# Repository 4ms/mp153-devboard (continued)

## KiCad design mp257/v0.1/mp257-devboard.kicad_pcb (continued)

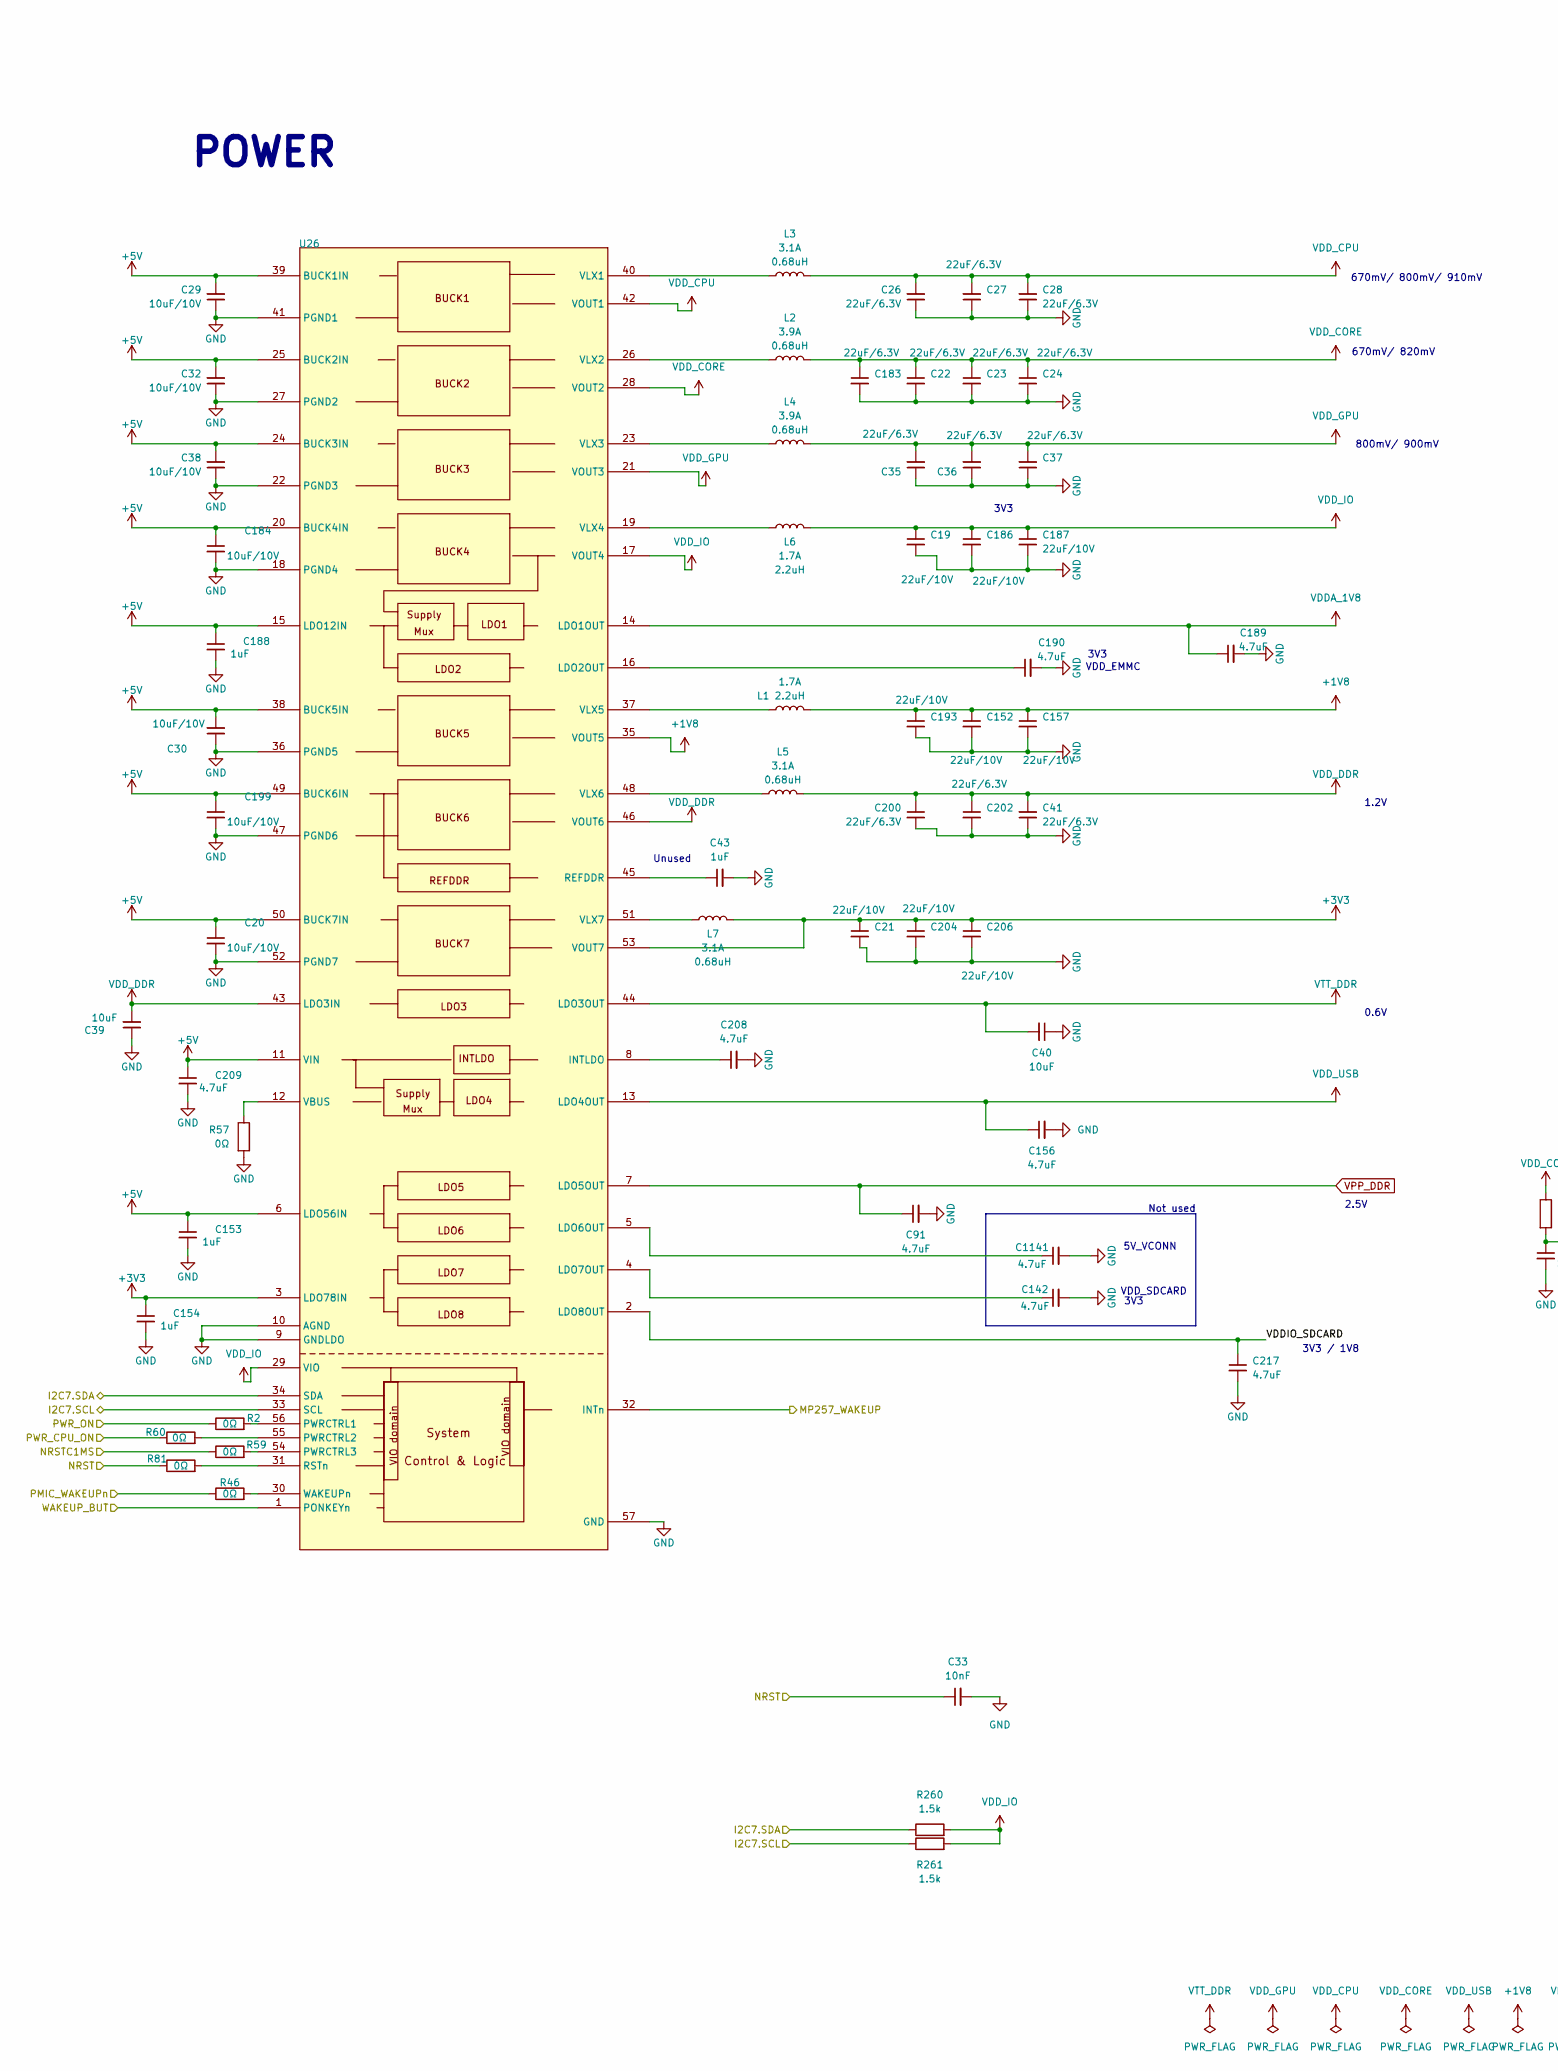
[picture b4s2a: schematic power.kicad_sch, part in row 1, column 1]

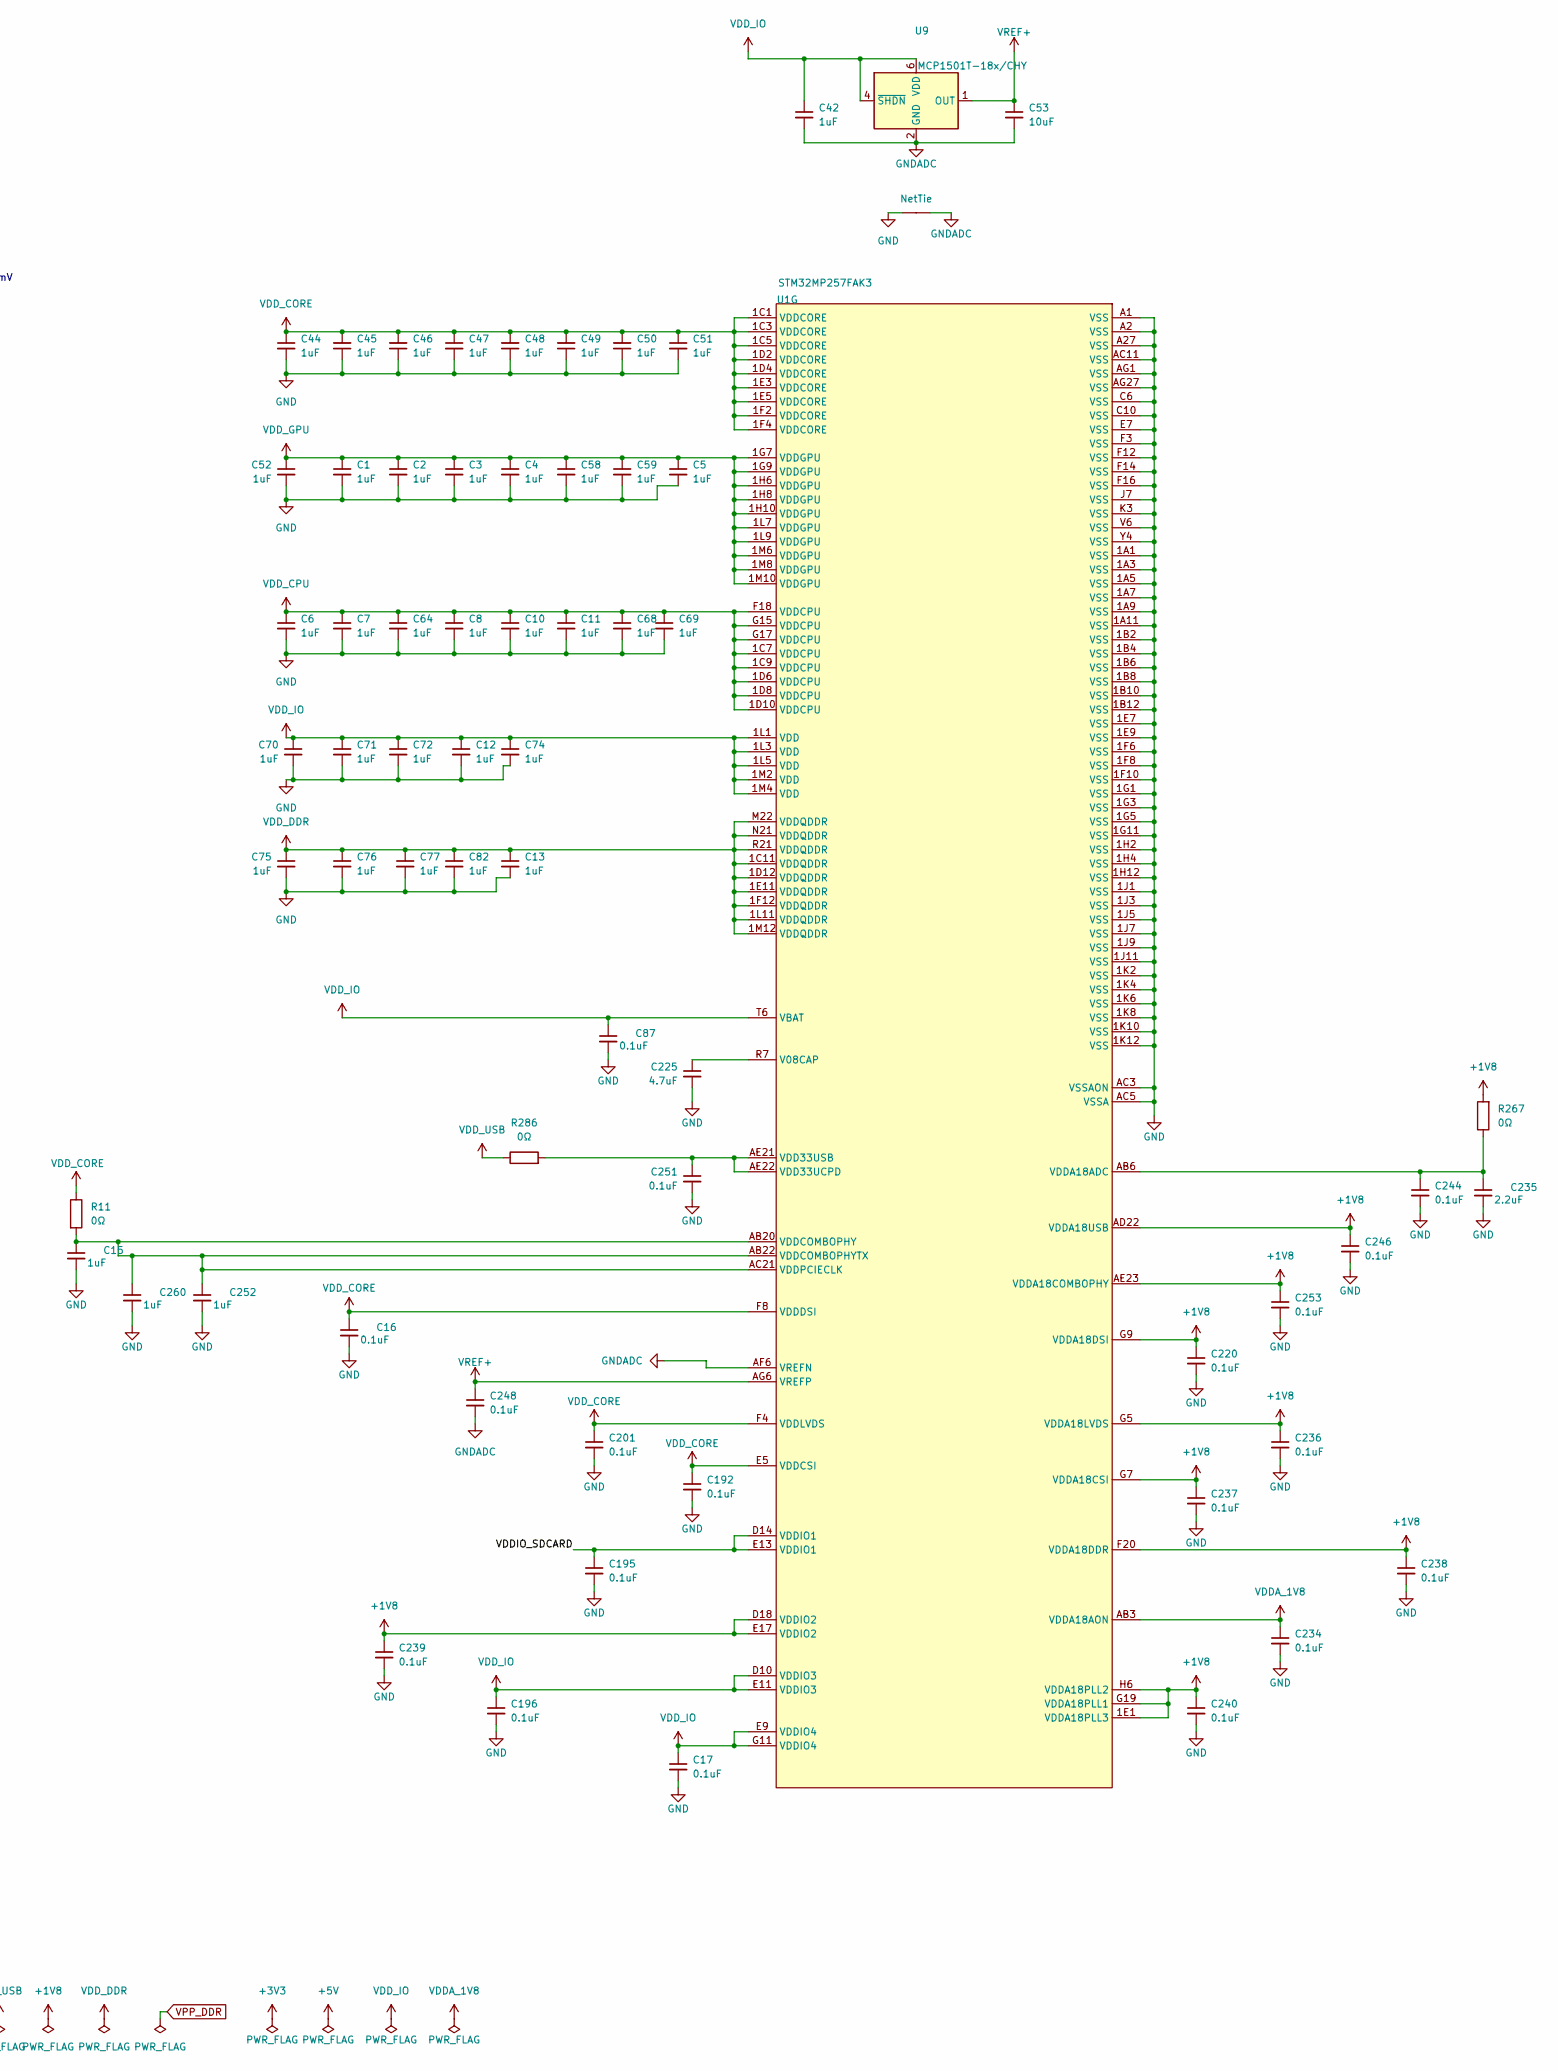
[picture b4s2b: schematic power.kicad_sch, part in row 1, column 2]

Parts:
C1, C2, C3, C4, C5, C6, C7, C8, C10, C11, C12, C13, C15, C44, C45, C46, C47, C48, C49, C50, C51, C52, C58, C59, C64, C68, C69, C70, C71, C72, C74, C75, C76, C77, C82, C252, C260: 1uF_0201_4V; C_0201_TightCourtyard; Part Number CC0201MRX5R5BB105; JLCPCB ID C272877
C16, C17, C192, C195, C196, C201, C220, C236, C237, C238, C239, C240, C244, C246, C248, C251, C253: 100nF_0201_16V; C_0201_TightCourtyard; Part Number GRT033C81E104KE01D; JLCPCB ID C711071
C19, C21, C152, C157, C186, C187, C193, C204, C206: 22uF_0805_10V; C_0805; Part Number LMK212BBJ226MG-T; JLCPCB ID C45783
C20, C29, C30, C32, C38, C184, C199: 10uF_0603_10V; C_0603; Part Number GRM188R61A106KE69D; JLCPCB ID C19702
C22, C23, C24, C26, C27, C28, C35, C36, C37, C41, C183, C200, C202: 22uF_0603_6.3V; C_0603; Part Number GRM188R60J226MEA0J; JLCPCB ID C59461
C33: 10nF_0402_16V; C_0402; Part Number CC0402KRX7R7BB103; JLCPCB ID C15195
C39, C40, C53: 10uF_0402_6.3V; C_0402; Part Number GRM155R61A106ME44D; JLCPCB ID C77000
C42, C43, C153, C154, C188: 1uF_0402_25V; C_0402; Part Number GMK105CC6105KV-F; JLCPCB ID C52923
C87, C234: 100nF_0402_16V; C_0402; Part Number GCM155R71C104KA55D; JLCPCB ID C1525
C91, C142, C156, C189, C190, C208, C209, C217, C1141: 4.7uF_0402_6.3V; C_0402; Part Number GRM155R60J475ME47; JLCPCB ID C23733
C225: 4.7uF_0201_6.3V; C_0201; Part Number GRM035R60J475ME15D; JLCPCB ID C335103
C235: 2.2uF_0201_10V; C_0201; Part Number GRM033R61A225ME47D; JLCPCB ID C319184
L1, L6: 2.2uH_1.7A_2016; COIL_2016_Murata_Handsolder; Part Number DFE201610E-2R2M=P2
L2, L4: 0.68uH_3.9A_2520; COIL_2520_TOKO_Handsolder; Part Number DFE252012F-R68M=P2
L3, L5, L7: 0.68uH_3.1A_2016; COIL_2016_Murata_Handsolder; Part Number DFE201610E-R68M=P2
NT2: NetTie; NetTie-2_SMD_Pad0.16mm_6mil; Part Number Do Not Place
R2, R11, R46, R57, R59, R60, R81, R267, R286: 0Ω_0402; R_0402; Part Number RC0402FR-070RL; JLCPCB ID C106231
R260, R261: 1.5k_0402; R_0402; Part Number RC0402FR-071K5L; JLCPCB ID C114759
U1: STM32MP257FAK3; TFBGA-424_14x14mm_P0.5_STM_AK; Part Number STM32MP257FAK3
U9: MCP1501T-18x/CHY; SOT-23-6; Part Number MCP1501T-18E/CHY; JLCPCB ID C150807
U26: STPMIC25APQR; QFN-56_EP_7x7_Pitch0.4mm; Part Number STPMIC25APQR

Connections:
+1V8: C152.1, C157.1, C193.1, C220.1, C236.1, C237.1, C238.1, C239.1, C240.1, C246.1, C253.1, L1.2, R267.2, U1.1E1 (VDDA18PLL3), U1.AD22 (VDDA18USB), U1.AE23 (VDDA18COMBOPHY), U1.D18 (VDDIO2), U1.E17 (VDDIO2), U1.F20 (VDDA18DDR), U1.G5 (VDDA18LVDS), U1.G7 (VDDA18CSI), U1.G9 (VDDA18DSI), U1.G19 (VDDA18PLL1), U1.H6 (VDDA18PLL2), U26.35 (VOUT5)
+3V3: C21.1, C154.1, C204.1, C206.1, L7.2, U26.3 (LDO78IN), U26.53 (VOUT7); also elsewhere on the board
+5V: C20.1, C29.2, C30.2, C32.2, C38.2, C153.1, C184.1, C188.1, C199.1, C209.1, U26.6 (LDO56IN), U26.11 (VIN), U26.15 (LDO12IN), U26.20 (BUCK4IN), U26.24 (BUCK3IN), U26.25 (BUCK2IN), U26.38 (BUCK5IN), U26.39 (BUCK1IN), U26.49 (BUCK6IN), U26.50 (BUCK7IN); also elsewhere on the board
/DFU_BOOT: U26.1 (PONKEYn); also elsewhere on the board
/I2C7.SCL: R261.1, U26.33 (SCL); also elsewhere on the board
/I2C7.SDA: R260.1, U26.34 (SDA); also elsewhere on the board
/MP257_WAKEUP: U26.32 (INTn); also elsewhere on the board
/NRST: C33.1, R81.1; also elsewhere on the board
/NRSTC1MS: R59.1; also elsewhere on the board
/PMIC_WAKEUPn: R46.1; also elsewhere on the board
/PWR_CPU_ON: R60.1; also elsewhere on the board
/PWR_ON: R2.1; also elsewhere on the board
/Power/VDDIO_SDCARD: C195.1, C217.1, U1.D14 (VDDIO1), U1.E13 (VDDIO1), U26.2 (LDO8OUT)
GND: C1.2, C2.2, C3.2, C4.2, C5.2, C6.2, C7.2, C8.2, C10.2, C11.2, C12.2, C13.2, C15.2, C16.2, C17.2, C19.2, C20.2, C21.2, C22.2, C23.2, C24.2, C26.1, C27.1, C28.1, C29.1, C30.1, C32.1, C33.2, C35.1, C36.1, C37.1, C38.1, C39.1, C40.1, C41.1, C43.2, C44.2, C45.1, C46.1, C47.2, C48.1, C49.1, C50.1, C51.2, C52.2, C58.2, C59.2, C64.2, C68.2, C69.2, C70.2, C71.2, C72.2, C74.2, C75.2, C76.2, C77.2, C82.2, C87.2, C91.2, C142.2, C152.2, C153.2, C154.2, C156.2, C157.2, C183.2, C184.2, C186.2, C187.2, C188.2, C189.2, C190.2, C192.2, C193.2, C195.2, C196.2, C199.2, C200.2, C201.2, C202.2, C204.2, C206.2, C208.2, C209.2, C217.2, C220.2, C225.2, C234.2, C235.2, C236.2, C237.2, C238.2, C239.2, C240.2, C244.2, C246.2, C251.2, C252.2, C253.2, C260.2, C1141.2, NT2.1, R57.2, U1.1A1 (VSS), U1.1A3 (VSS), U1.1A5 (VSS), U1.1A7 (VSS), U1.1A9 (VSS), U1.1A11 (VSS), U1.1B2 (VSS), U1.1B4 (VSS), U1.1B6 (VSS), U1.1B8 (VSS), U1.1B10 (VSS), U1.1B12 (VSS), U1.1E7 (VSS), U1.1E9 (VSS), U1.1F6 (VSS), U1.1F8 (VSS), U1.1F10 (VSS), U1.1G1 (VSS), U1.1G3 (VSS), U1.1G5 (VSS), U1.1G11 (VSS), U1.1H2 (VSS), U1.1H4 (VSS), U1.1H12 (VSS), U1.1J1 (VSS), U1.1J3 (VSS), U1.1J5 (VSS), U1.1J7 (VSS), U1.1J9 (VSS), U1.1J11 (VSS), U1.1K2 (VSS), U1.1K4 (VSS), U1.1K6 (VSS), U1.1K8 (VSS), U1.1K10 (VSS), U1.1K12 (VSS), U1.A1 (VSS), U1.A2 (VSS), U1.A27 (VSS), U1.AC3 (VSSAON), U1.AC5 (VSSA), U1.AC11 (VSS), U1.AG1 (VSS), U1.AG27 (VSS), U1.C6 (VSS), U1.C10 (VSS), U1.E7 (VSS), U1.F3 (VSS), U1.F12 (VSS), U1.F14 (VSS), U1.F16 (VSS), U1.J7 (VSS), U1.K3 (VSS), U1.V6 (VSS), U1.Y4 (VSS), U26.9 (GNDLDO), U26.10 (AGND), U26.18 (PGND4), U26.22 (PGND3), U26.27 (PGND2), U26.36 (PGND5), U26.41 (PGND1), U26.47 (PGND6), U26.52 (PGND7), U26.57 (GND); also elsewhere on the board
GNDADC: C42.2, C53.2, C248.2, NT2.2, U1.AF6 (VREFN), U9.2 (GND), U9.3 (GND), U9.5 (GND); also elsewhere on the board
unnamed: C225.1, U1.R7 (V08CAP)
unnamed: C251.1, R286.2, U1.AE21 (VDD33USB), U1.AE22 (VDD33UCPD)
unnamed: C235.1, C244.1, R267.1, U1.AB6 (VDDA18ADC)
unnamed: C15.1, C252.1, C260.1, R11.2, U1.AB20 (VDDCOMBOPHY), U1.AB22 (VDDCOMBOPHYTX), U1.AC21 (VDDPCIECLK)
unnamed: C208.1, U26.8 (INTLDO)
unnamed: C190.1, U26.16 (LDO2OUT)
unnamed: C1141.1, U26.5 (LDO6OUT)
unnamed: C142.1, U26.4 (LDO7OUT)
unnamed: R2.2, U26.56 (PWRCTRL1)
unnamed: R60.2, U26.55 (PWRCTRL2)
unnamed: R59.2, U26.54 (PWRCTRL3)
unnamed: C43.1, U26.45 (REFDDR)
unnamed: R81.2, U26.31 (RSTn)
unnamed: R57.1, U26.12 (VBUS)
unnamed: L3.1, U26.40 (VLX1)
unnamed: L2.1, U26.26 (VLX2)
unnamed: L4.1, U26.23 (VLX3)
unnamed: L6.1, U26.19 (VLX4)
unnamed: L1.1, U26.37 (VLX5)
unnamed: L5.1, U26.48 (VLX6)
unnamed: L7.1, U26.51 (VLX7)
unnamed: R46.2, U26.30 (WAKEUPn)
VDDA_1V8: C189.1, C234.1, U1.AB3 (VDDA18AON), U26.14 (LDO1OUT); also elsewhere on the board
VDD_CORE: C16.1, C22.1, C23.1, C24.1, C44.1, C45.2, C46.2, C47.1, C48.2, C49.2, C50.2, C51.1, C183.1, C192.1, C201.1, L2.2, R11.1, U1.1C1 (VDDCORE), U1.1C3 (VDDCORE), U1.1C5 (VDDCORE), U1.1D2 (VDDCORE), U1.1D4 (VDDCORE), U1.1E3 (VDDCORE), U1.1E5 (VDDCORE), U1.1F2 (VDDCORE), U1.1F4 (VDDCORE), U1.E5 (VDDCSI), U1.F4 (VDDLVDS), U1.F8 (VDDDSI), U26.28 (VOUT2)
VDD_CPU: C6.1, C7.1, C8.1, C10.1, C11.1, C26.2, C27.2, C28.2, C64.1, C68.1, C69.1, L3.2, U1.1C7 (VDDCPU), U1.1C9 (VDDCPU), U1.1D6 (VDDCPU), U1.1D8 (VDDCPU), U1.1D10 (VDDCPU), U1.F18 (VDDCPU), U1.G15 (VDDCPU), U1.G17 (VDDCPU), U26.42 (VOUT1)
VDD_DDR: C13.1, C39.2, C41.2, C75.1, C76.1, C77.1, C82.1, C200.1, C202.1, L5.2, U1.1C11 (VDDQDDR), U1.1D12 (VDDQDDR), U1.1E11 (VDDQDDR), U1.1F12 (VDDQDDR), U1.1L11 (VDDQDDR), U1.1M12 (VDDQDDR), U1.M22 (VDDQDDR), U1.N21 (VDDQDDR), U1.R21 (VDDQDDR), U26.43 (LDO3IN), U26.46 (VOUT6); also elsewhere on the board
VDD_GPU: C1.1, C2.1, C3.1, C4.1, C5.1, C35.2, C36.2, C37.2, C52.1, C58.1, C59.1, L4.2, U1.1G7 (VDDGPU), U1.1G9 (VDDGPU), U1.1H6 (VDDGPU), U1.1H8 (VDDGPU), U1.1H10 (VDDGPU), U1.1L7 (VDDGPU), U1.1L9 (VDDGPU), U1.1M6 (VDDGPU), U1.1M8 (VDDGPU), U1.1M10 (VDDGPU), U26.21 (VOUT3)
VDD_IO: C12.1, C17.1, C19.1, C42.1, C70.1, C71.1, C72.1, C74.1, C87.1, C186.1, C187.1, C196.1, L6.2, R260.2, R261.2, U1.1L1 (VDD), U1.1L3 (VDD), U1.1L5 (VDD), U1.1M2 (VDD), U1.1M4 (VDD), U1.D10 (VDDIO3), U1.E9 (VDDIO4), U1.E11 (VDDIO3), U1.G11 (VDDIO4), U1.T6 (VBAT), U9.4 (~SHDN), U9.6 (VDD), U26.17 (VOUT4), U26.29 (VIO); also elsewhere on the board
VDD_USB: C156.1, R286.1, U26.13 (LDO4OUT)
VPP_DDR: C91.1, U26.7 (LDO5OUT); also elsewhere on the board
VREF+: C53.1, C248.1, U1.AG6 (VREFP), U9.1 (OUT); also elsewhere on the board
VTT_DDR: C40.2, U26.44 (LDO3OUT); also elsewhere on the board

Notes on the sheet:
3V3
Not used
POWER
1.2V
2.5V
670mV/ 820mV
800mV/ 900mV
3V3 / 1V8
VDD_SDCARD
Unused
5V_VCONN
VDD_EMMC
0.6V
670mV/ 800mV/ 910mV

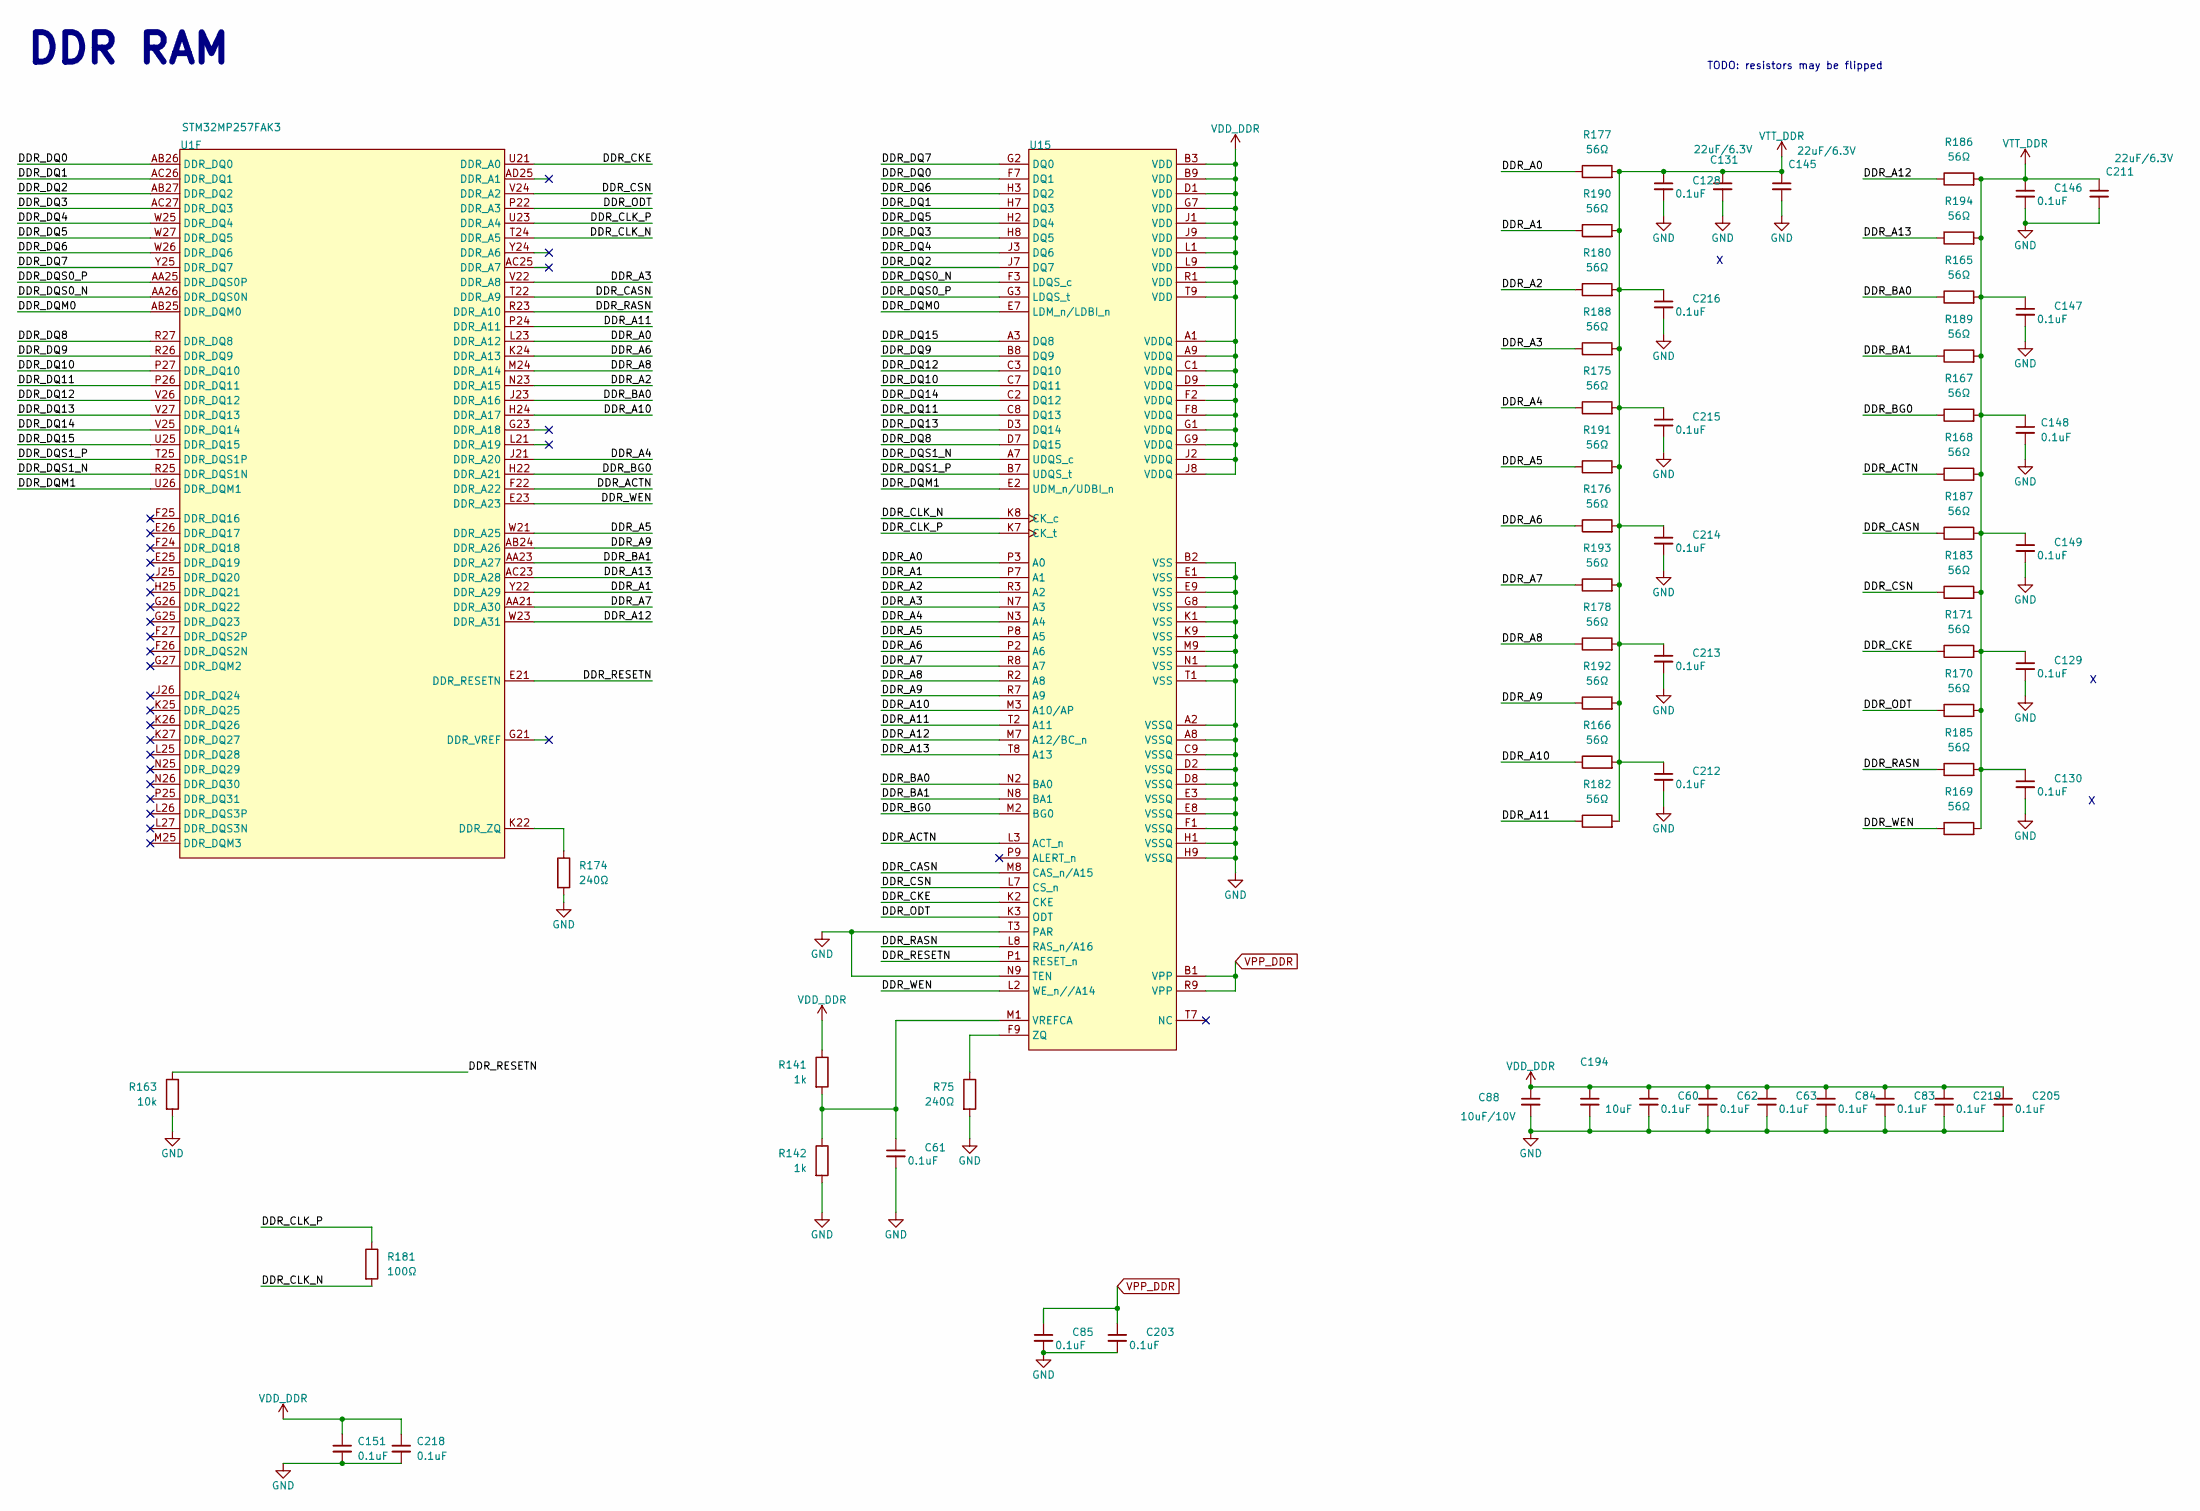
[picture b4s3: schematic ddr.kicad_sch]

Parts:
C60, C61, C62, C63, C83, C84, C85, C128, C129, C130, C146, C147, C148, C149, C151, C203, C205, C212, C213, C214, C215, C216, C218, C219: 100nF_0402_16V; C_0402; Part Number GCM155R71C104KA55D; JLCPCB ID C1525
C88: 10uF_0603_10V; C_0603; Part Number GRM188R61A106KE69D; JLCPCB ID C19702
C131, C145, C211: 22uF_0603_6.3V; C_0603; Part Number GRM188R60J226MEA0J; JLCPCB ID C59461
C194: 10uF_0402_6.3V; C_0402; Part Number GRM155R61A106ME44D; JLCPCB ID C77000
R75: 240Ω_0402; R_0402; Part Number RC0402FR-07240RL; JLCPCB ID C114755
R141, R142: 1k_0402; R_0402; Part Number RC0402FR-071KL; JLCPCB ID C106235
R163: 10k_0402; R_0402; Part Number RC0402FR-0710KL; JLCPCB ID C60490
R165, R166, R167, R168, R169, R170, R171, R175, R176, R177, R178, R180, R182, R183, R185, R186, R187, R188, R189, R190, R191, R192, R193, R194: 56Ω_0402; R_0402; Part Number RC0402FR-0756RL; JLCPCB ID C137957
R174: 240Ω_0201; R_0201_0603Metric; Part Number RC0201FR-07240RL; JLCPCB ID C155745
R181: 100Ω_0402; R_0402; Part Number RC0402FR-07100RL; JLCPCB ID C106232
U1: STM32MP257FAK3; TFBGA-424_14x14mm_P0.5_STM_AK; Part Number STM32MP257FAK3
U15: MT40A1G16TB-062E IT:F; FBGA-96_Layout2x3x16_Body8x14_P0.8mm; Part Number 2 IS43QR16256B-075UBLI

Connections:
/DDR/DDR_A0: R177.1, U1.L23 (DDR_A12), U15.P3 (A0)
/DDR/DDR_A1: R190.1, U1.Y22 (DDR_A29), U15.P7 (A1)
/DDR/DDR_A2: R180.1, U1.N23 (DDR_A15), U15.R3 (A2)
/DDR/DDR_A3: R188.1, U1.V22 (DDR_A8), U15.N7 (A3)
/DDR/DDR_A4: R175.1, U1.J21 (DDR_A20), U15.N3 (A4)
/DDR/DDR_A5: R191.1, U1.W21 (DDR_A25), U15.P8 (A5)
/DDR/DDR_A6: R176.1, U1.K24 (DDR_A13), U15.P2 (A6)
/DDR/DDR_A7: R193.1, U1.AA21 (DDR_A30), U15.R8 (A7)
/DDR/DDR_A8: R178.1, U1.M24 (DDR_A14), U15.R2 (A8)
/DDR/DDR_A9: R192.1, U1.AB24 (DDR_A26), U15.R7 (A9)
/DDR/DDR_A10: R166.1, U1.H24 (DDR_A17), U15.M3 (A10/AP)
/DDR/DDR_A11: R182.1, U1.P24 (DDR_A11), U15.T2 (A11)
/DDR/DDR_A12: R186.1, U1.W23 (DDR_A31), U15.M7 (A12/BC_n)
/DDR/DDR_A13: R194.1, U1.AC23 (DDR_A28), U15.T8 (A13)
/DDR/DDR_ACTN: R168.1, U1.F22 (DDR_A22), U15.L3 (ACT_n)
/DDR/DDR_BA0: R165.1, U1.J23 (DDR_A16), U15.N2 (BA0)
/DDR/DDR_BA1: R189.1, U1.AA23 (DDR_A27), U15.N8 (BA1)
/DDR/DDR_BG0: R167.1, U1.H22 (DDR_A21), U15.M2 (BG0)
/DDR/DDR_CASN: R187.1, U1.T22 (DDR_A9), U15.M8 (CAS_n/A15)
/DDR/DDR_CKE: R171.1, U1.U21 (DDR_A0), U15.K2 (CKE)
/DDR/DDR_CLK_N: R181.2, U1.T24 (DDR_A5), U15.K8 (CK_c)
/DDR/DDR_CLK_P: R181.1, U1.U23 (DDR_A4), U15.K7 (CK_t)
/DDR/DDR_CSN: R183.1, U1.V24 (DDR_A2), U15.L7 (CS_n)
/DDR/DDR_DQ0: U1.AB26 (DDR_DQ0), U15.F7 (DQ1)
/DDR/DDR_DQ1: U1.AC26 (DDR_DQ1), U15.H7 (DQ3)
/DDR/DDR_DQ2: U1.AB27 (DDR_DQ2), U15.J7 (DQ7)
/DDR/DDR_DQ3: U1.AC27 (DDR_DQ3), U15.H8 (DQ5)
/DDR/DDR_DQ4: U1.W25 (DDR_DQ4), U15.J3 (DQ6)
/DDR/DDR_DQ5: U1.W27 (DDR_DQ5), U15.H2 (DQ4)
/DDR/DDR_DQ6: U1.W26 (DDR_DQ6), U15.H3 (DQ2)
/DDR/DDR_DQ7: U1.Y25 (DDR_DQ7), U15.G2 (DQ0)
/DDR/DDR_DQ8: U1.R27 (DDR_DQ8), U15.D7 (DQ15)
/DDR/DDR_DQ9: U1.R26 (DDR_DQ9), U15.B8 (DQ9)
/DDR/DDR_DQ10: U1.P27 (DDR_DQ10), U15.C7 (DQ11)
/DDR/DDR_DQ11: U1.P26 (DDR_DQ11), U15.C8 (DQ13)
/DDR/DDR_DQ12: U1.V26 (DDR_DQ12), U15.C3 (DQ10)
/DDR/DDR_DQ13: U1.V27 (DDR_DQ13), U15.D3 (DQ14)
/DDR/DDR_DQ14: U1.V25 (DDR_DQ14), U15.C2 (DQ12)
/DDR/DDR_DQ15: U1.U25 (DDR_DQ15), U15.A3 (DQ8)
/DDR/DDR_DQM0: U1.AB25 (DDR_DQM0), U15.E7 (LDM_n/LDBI_n)
/DDR/DDR_DQM1: U1.U26 (DDR_DQM1), U15.E2 (UDM_n/UDBI_n)
/DDR/DDR_DQS0_N: U1.AA26 (DDR_DQS0N), U15.F3 (LDQS_c)
/DDR/DDR_DQS0_P: U1.AA25 (DDR_DQS0P), U15.G3 (LDQS_t)
/DDR/DDR_DQS1_N: U1.R25 (DDR_DQS1N), U15.A7 (UDQS_c)
/DDR/DDR_DQS1_P: U1.T25 (DDR_DQS1P), U15.B7 (UDQS_t)
/DDR/DDR_ODT: R170.1, U1.P22 (DDR_A3), U15.K3 (ODT)
/DDR/DDR_RASN: R185.1, U1.R23 (DDR_A10), U15.L8 (RAS_n/A16)
/DDR/DDR_RESETN: R163.1, U1.E21 (DDR_RESETN), U15.P1 (RESET_n)
/DDR/DDR_WEN: R169.1, U1.E23 (DDR_A23), U15.L2 (WE_n//A14)
GND: C60.2, C61.2, C62.2, C63.2, C83.2, C84.2, C85.2, C88.2, C128.2, C129.2, C130.2, C131.2, C145.2, C146.2, C147.2, C148.2, C149.2, C151.2, C194.2, C203.2, C205.2, C211.2, C212.2, C213.2, C214.2, C215.2, C216.2, C218.2, C219.2, R75.2, R142.2, R163.2, R174.2, U15.A2 (VSSQ), U15.A8 (VSSQ), U15.B2 (VSS), U15.C9 (VSSQ), U15.D2 (VSSQ), U15.D8 (VSSQ), U15.E1 (VSS), U15.E3 (VSSQ), U15.E8 (VSSQ), U15.E9 (VSS), U15.F1 (VSSQ), U15.G8 (VSS), U15.H1 (VSSQ), U15.H9 (VSSQ), U15.K1 (VSS), U15.K9 (VSS), U15.M9 (VSS), U15.N1 (VSS), U15.N9 (TEN), U15.T1 (VSS), U15.T3 (PAR); also elsewhere on the board
unnamed: R174.1, U1.K22 (DDR_ZQ)
unnamed: C61.1, R141.2, R142.1, U15.M1 (VREFCA)
unnamed: R75.1, U15.F9 (ZQ)
VDD_DDR: C60.1, C62.1, C63.1, C83.1, C84.1, C88.1, C151.1, C194.1, C205.1, C218.1, C219.1, R141.1, U15.A1 (VDDQ), U15.A9 (VDDQ), U15.B3 (VDD), U15.B9 (VDD), U15.C1 (VDDQ), U15.D1 (VDD), U15.D9 (VDDQ), U15.F2 (VDDQ), U15.F8 (VDDQ), U15.G1 (VDDQ), U15.G7 (VDD), U15.G9 (VDDQ), U15.J1 (VDD), U15.J2 (VDDQ), U15.J8 (VDDQ), U15.J9 (VDD), U15.L1 (VDD), U15.L9 (VDD), U15.R1 (VDD), U15.T9 (VDD); also elsewhere on the board
VPP_DDR: C85.1, C203.1, U15.B1 (VPP), U15.R9 (VPP); also elsewhere on the board
VTT_DDR: C128.1, C129.1, C130.1, C131.1, C145.1, C146.1, C147.1, C148.1, C149.1, C211.1, C212.1, C213.1, C214.1, C215.1, C216.1, R165.2, R166.2, R167.2, R168.2, R169.2, R170.2, R171.2, R175.2, R176.2, R177.2, R178.2, R180.2, R182.2, R183.2, R185.2, R186.2, R187.2, R188.2, R189.2, R190.2, R191.2, R192.2, R193.2, R194.2; also elsewhere on the board

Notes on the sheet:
TODO: resistors may be flipped
DDR RAM

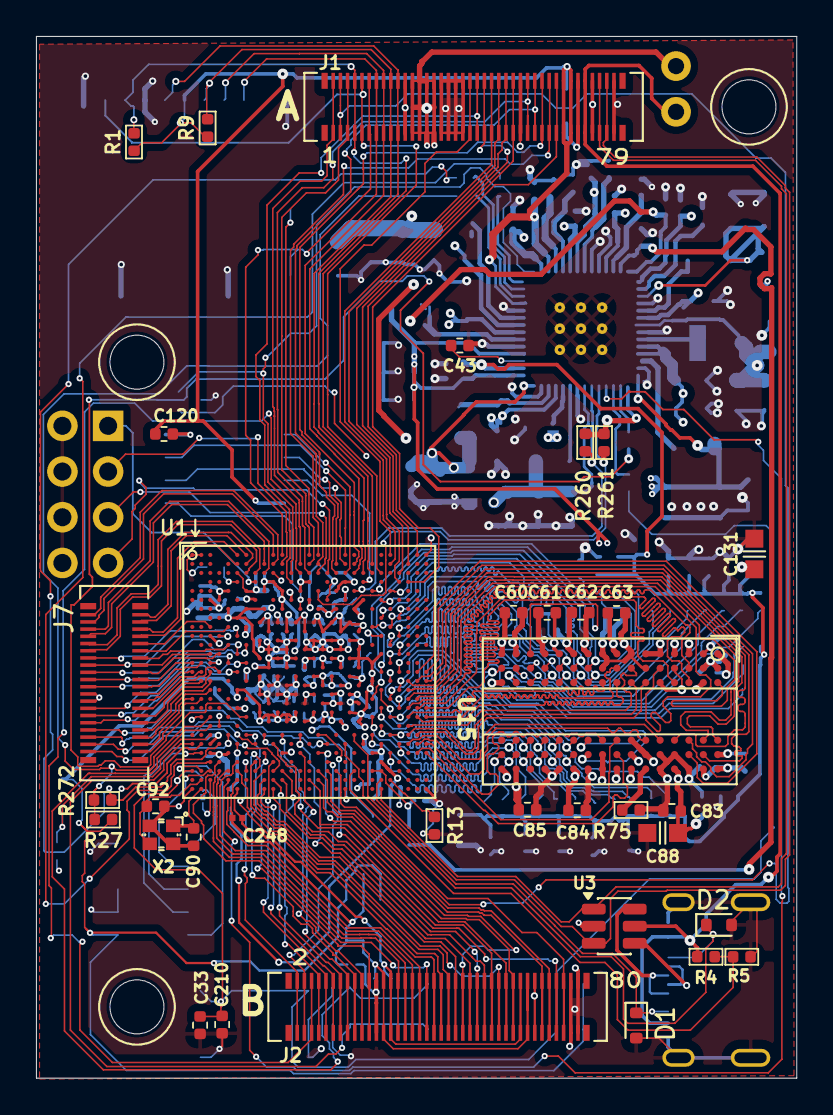
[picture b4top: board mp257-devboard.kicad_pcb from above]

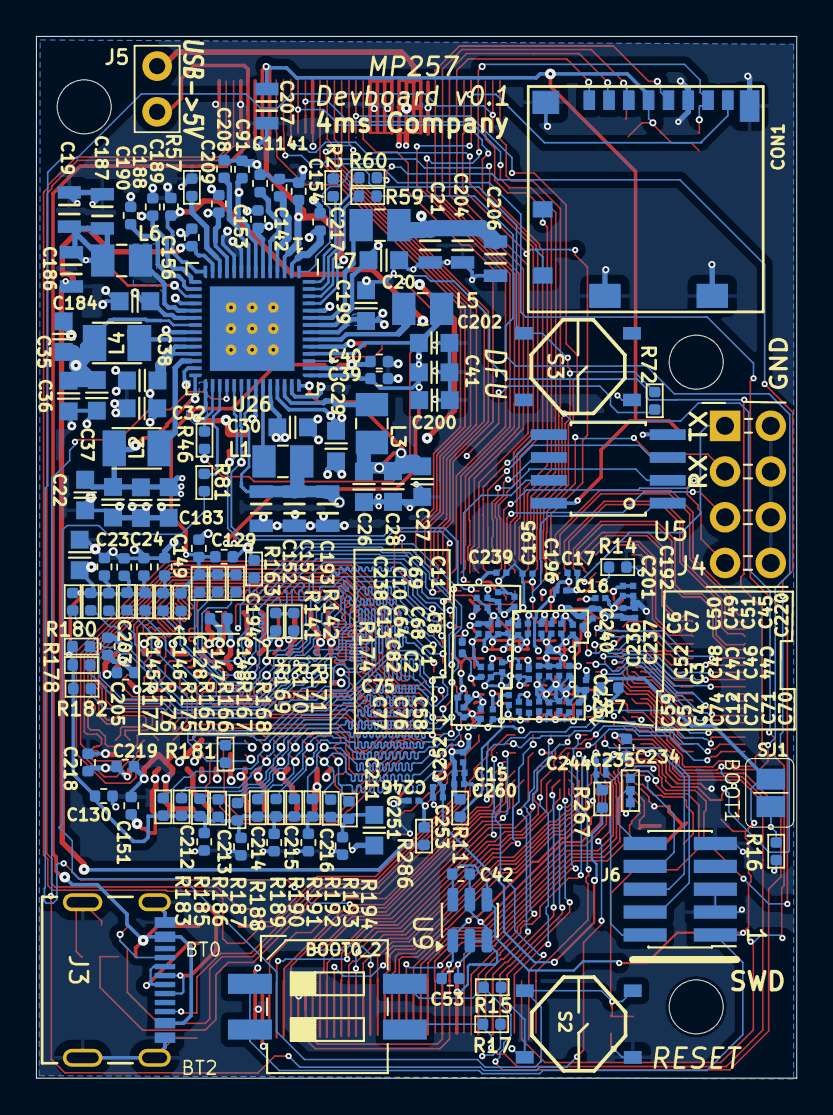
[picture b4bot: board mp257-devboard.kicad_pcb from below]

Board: 4 copper layers, 42.2 x 57.9 mm, 225 parts (187 on the bottom side), 223 nets.

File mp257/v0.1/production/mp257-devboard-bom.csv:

"4ms Company"
"PCBA Project:","mp257-devboard","Revision: ","v0.1"
"EMAIL:","4ms@4mscompany.com"
"DATE:","2026-04-01"

"Group","Item#","Manufacturer","Manufacter Part#","Designator","Quantity","Designation","Package","Comments","Supplied by:"
"","1","","","D1, D2","2","ESD5Zxx","D_SOD-523",""
"","2","Hirose","DF40C-80DP-0.4V(51)","J1, J2","2","Pins_02x40_P0.4mm_W3.0mm_SMT","Connector-80pin-P0.4mm-W3.0mm",""
"","3","Molex","217179-0001","J3","1","USB-C_Receptacle_Molex_2171790001","USB_C_Receptacle_Molex_2171790001",""
"","4","","","J7","1","Conn_02x20_Odd_Even","Connector-40pin-P0.4mm-W3.0mm",""
"","5","","","SJ1","1","Jumper","JUMPER_SMD_1x2",""
"","6","STMICROELECTRONICS","STM32MP257FAK3","U1","1","STM32MP257FAK3 MPU","TFBGA-424_14x14mm_P0.5_STM_AK",""
"","7","","","U9","1","MCP1501-18xCH","SOT-23-6",""
"","8","Winbond","W664GG6RB","U15","1","MT40A1G16TB-062E IT:F","FBGA-96_Layout2x3x16_Body8x14_P0.8mm",""
"","9","STMICROELECTRONICS","STPMIC25APQR","U26","1","STPMIC25APQR","QFN-56_EP_7x7_Pitch0.4mm",""
"A","10","CTS","219-2MST","BOOT0_2","1","SW_DIP_x02_CTS_219-2MST, DIP Switch SPST x 2, Gull wing P2.54mm, 6.7x6.55mm Body, 8.6mm Rows","SW_DIP_SPSTx02_CTS_219-2MSTR",""
"A","11","Yageo","CC0201MRX5R5BB105","C1, C2, C3, C4, C5, C6, C7, C8, C10, C11, C12, C13, C15, C44, C45, C46, C47, C48, C49, C50, C51, C52, C58, C59, C64, C68, C69, C70, C71, C72, C74, C75, C76, C77, C82, C252, C260","37","1uF_0201_4V, 1uF, Min. 4V 10%, X7R or X5R or X6S or similar","C0201_TightCourtyard",""
"A","12","Murata","GRT033C81E104KE01D","C16, C17, C192, C195, C196, C201, C220, C236, C237, C238, C239, C240, C244, C246, C248, C251, C253","17","100nF_0201_16V, 0.1uF, Min. 16V 10%, X7R or X5R or X6S or similar","C0201_TightCourtyard",""
"A","13","Taiyo Yuden","LMK212BBJ226MG-T","C19, C21, C152, C157, C186, C187, C193, C204, C206, C207","10","22uF_0805_10V, 22uF, Min. 10V, 20%, X5R or X7S or similar, 0805, MLCC","C0805",""
"A","14","Murata","GRM188R61A106KE69D","C20, C29, C30, C32, C38, C88, C184, C199","8","10uF_0603_10V, 10uF, Min. 10V X5R 10%","C0603",""
"A","15","Murata","GRM188R60J226MEA0J","C22, C23, C24, C26, C27, C28, C35, C36, C37, C41, C131, C145, C183, C200, C202, C211","16","22uF_0603_6.3V, 22uF, 6.3V,10%,X5R or X7R,0603","C0603",""
"A","16","Yageo","CC0402KRX7R7BB103","C33","1","10nF_0402_16V, 10nF, Min. 16V 10%, X7R or X5R or similar","C0402",""
"A","17","","","C39, C40, C53, C194","4","10uF_0402_6.3V, 10uF, Min. 6.3V, 0402, Ceramic/MLCC","C0402",""
"A","18","Taiyo Yuden","GMK105CC6105KV-F","C42, C43, C153, C154, C188","5","1uF_0402_25V, 1uF, Min. 25V, 0402, Ceramic/MLCC","C0402",""
"A","19","Murata","GCM155R71C104KA55D","C60, C61, C62, C63, C83, C84, C85, C87, C120, C128, C129, C130, C146, C147, C148, C149, C151, C203, C205, C210, C212, C213, C214, C215, C216, C218, C219, C234","28","100nF_0402_16V, 0.1uF, Min. 16V 10%, X7R or X5R or similar","C0402",""
"A","20","Yageo","CC0402CRNPO9BN6R8","C90, C92","2","6.8pF_0402_25V, 6.8pF, Min. 25V 10%, NP0/C0G","C0402",""
"A","21","Murata","GRM155R60J475ME47","C91, C142, C156, C189, C190, C208, C209, C217, C1141","9","4.7uF_0402_6.3V, 4.7uF, Min. 6.3V 20%, X7R or X5R or similar","C0402",""
"A","22","","","C225","1","4.7uF_0201_6.3V, 4.7uF, Min. 6.3V 10%, X7R or X5R or X6S or similar","C0201_TightCourtyard",""
"A","23","","","C235","1","2.2uF_0201_10V, 2.2uF, Min. 10V 10%, X7R or X5R or X6S or similar","C0201_TightCourtyard",""
"A","24","Murata","DFE201610E-2R2M=P2","L1, L6","2","2.2uH_1.7A_2016, 2.2uH, Isat>2.4A, Imax>=1.7A, Rdc<=120mOhms, shielded","COIL_2016_Murata_Handsolder",""
"A","25","Murata","DFE252012F-R68M=P2","L2, L4","2","0.68uH_3.9A_2520, 0.68uH, Isat>5.4A, Imax>=3.9A, Rdc<=50mOhms, shielded","COIL_2520_TOKO_Handsolder",""
"A","26","Murata","DFE201610E-R68M=P2","L3, L5, L7","3","0.68uH_3.1A_2016, 0.68uH, Isat>4.3A, Imax>=3.1A, Rdc<=50mOhms, shielded","COIL_2016_Murata_Handsolder",""
"A","27","Yageo","RC0402FR-0710KL","R1, R9, R15, R16, R17, R27, R72, R163, R272","9","10k_0402, 10k, 1%, 1/16W, 0402","R0402",""
"A","28","Yageo","RC0402FR-070RL","R2, R11, R46, R57, R59, R60, R81, R267, R286","9","0Ω_0402, 0Ω, 1%, 1/16W, 0402","R0402",""
"A","29","Yageo","RC0402FR-07430KL","R4","1","430k_0402, 430k, 1%, 1/16W, 0402","R0402",""
"A","30","Yageo","RC0402FR-07620KL","R5","1","620k_0402, 620k, 1%, 1/16W, 0402","R0402",""
"A","31","Yageo","RC0402FR-07200RL","R13, R14","2","200Ω_0402, 200Ω, 1%, 1/16W, 0402","R0402",""
"A","32","Yageo","RC0402FR-07240RL","R75","1","240Ω_0402, 240Ω, 1%, 1/16W, 0402","R0402",""
"A","33","Yageo","RC0402FR-071KL","R141, R142","2","1k_0402, 1k, 1%, 1/16W, 0402","R0402",""
"A","34","Yageo","RC0402FR-0756RL","R165, R166, R167, R168, R169, R170, R171, R175, R176, R177, R178, R180, R182, R183, R185, R186, R187, R188, R189, R190, R191, R192, R193, R194","24","56Ω_0402, 56Ω, 1%, 1/16W, 0402","R0402",""
"A","35","","","R174","1","240Ω_0201, 240Ω, 5%, 0201","R0201_0603Metric",""
"A","36","Yageo","RC0402FR-07100RL","R181","1","100Ω_0402, 100Ω, 1%, 1/16W, 0402","R0402",""
"A","37","Yageo","RC0402FR-071K5L","R260, R261","2","1.5k_0402, 1.5k, 1%, 1/16W, 0402","R0402",""
"A","38","C&K Switches","PTS526 SM15 SMTR2 LFS","S2, S3","2","SW_Push_PTS526 SM15 SMTR2 LFS, Tact button, NO, ","Button_Tact_PTS526",""
"A","39","STMicroelectronics","USBLC6-2SC6","U3","1","USBLC6-2SC6, ESD Protection, pins 3+4, 1+6 shorted","SOT-23-6",""
"A","40","Winbond","W25Q128JVSIQ","U5","1","NORFLASH_W25Q128JV, 16Mbit QSPI NOR FLASH, 4kb uniform sectors","SOIC-8_5.28x4.9mm_Pitch1.27mm",""
"A","41","ECS","","X2","1","40MHz_6.8pF_2x1.6mm, 40MHz 6.8pF Crystal Resonator, 10ppm, 2016 2x1.6mm","Crystal_2.0x1.6mm_4pin",""
"AB","42","Molex","104031-0811","CON1","1","microSDCon_SMT_104031-0811, MicroSD Card Conn Horiz SMT","CardSlot_MicroSD_Molex_104031-0811",""
"AB","43","Samtec","FTSH-105-01-F-DV","J6","1","Pins_02x05_P1.27mm_SMT, Header 2x5 Pins, Pitch=1.27mm, Pin Height=3mm, Vertical, SMT","Pins_2x05_1.27mm_SMD",""
"B","44","Samtec","TSW-104-08-T-D-RA","J4","1","Pins_02x04_RightAngle_P2.54mm_TH, HEADER 2x4 MALE PINS 0.100” 90deg Right Angle","Pins_2x04_P2.54mm_Horizontal_CroppedSilk",""
"B","45","Samtec","TSW-102-08-T-S-RA","J5","1","Pins_01x02_RightAngle_P2.54mm_TH, HEADER 1x2 MALE PINS 0.100” 90deg","Pins_1x02_2.54mm_TH",""
"E","46","McMaster-Carr","93657A504","H1, H2, H3","3","Spacer Nylon, Unthreaded, Height=11mm, ID >= 3mm, OD < 6mm","MountingHole_Generic_3mm",""
